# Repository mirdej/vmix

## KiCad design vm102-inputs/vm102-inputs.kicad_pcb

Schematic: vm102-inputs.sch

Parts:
C101: C; C_0603_1608Metric_Pad1.05x0.95mm_HandSolder
D101, D102: SK6812MINI; LED_SK6812MINI_PLCC4_3.5x3.5mm_P1.75mm
J101, J102, J103, J104, J105, J109, J110, J111: Conn; TestPoint_THTPad_D4.0mm_Drill2.0mm
J106: Conn_01x33_Shielded; Molex_502231-3300_1x33-1SH_P0.5mm_Vertical
J107: Conn; TestPoint_THTPad_D3.0mm_Drill1.5mm
SW101, SW102: SW_SPDT; PinSocket_1x03_P2.54mm_Vertical

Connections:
/a: J106.12, J109.1
/aux: J105.1, J106.18
/b: J106.14, J110.1
/bias: J106.22, J107.1
/c: J106.16, J111.1
/compa-out: J102.1, J106.2
/hi_clip1: J106.8, SW102.1 (A)
/hi_clip2: J106.7, SW102.2 (B)
/lo_clip1: J106.4, SW101.1 (A)
/lo_clip2: J106.5, SW101.2 (B)
/output: J103.1, J106.6
/pixels: D101.3 (DIN), J106.10
/scale: J104.1, J106.20
/siff-in: J101.1, J106.24
GND: C101.2, D101.2 (VSS), D102.2 (VSS), J106.1, J106.3, J106.9, J106.13, J106.15, J106.17, J106.19, J106.21, J106.23
unnamed: D101.1 (DOUT), D102.3 (DIN)
VCC: C101.1, D101.4 (VDD), D102.4 (VDD), J106.11

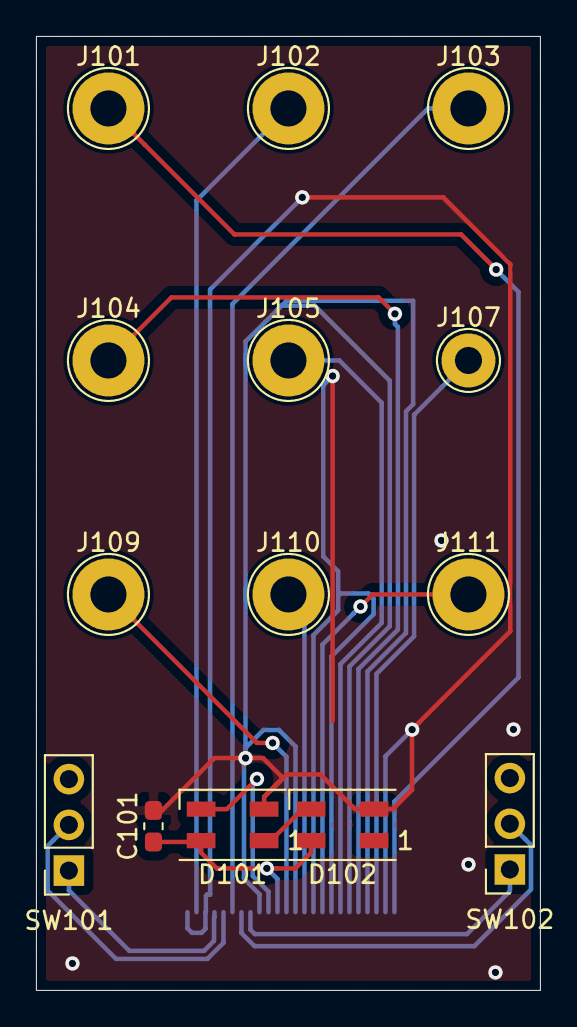
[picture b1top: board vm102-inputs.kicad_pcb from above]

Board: 2 copper layers, 28.0 x 53.0 mm, 15 parts (1 on the bottom side), 17 nets.

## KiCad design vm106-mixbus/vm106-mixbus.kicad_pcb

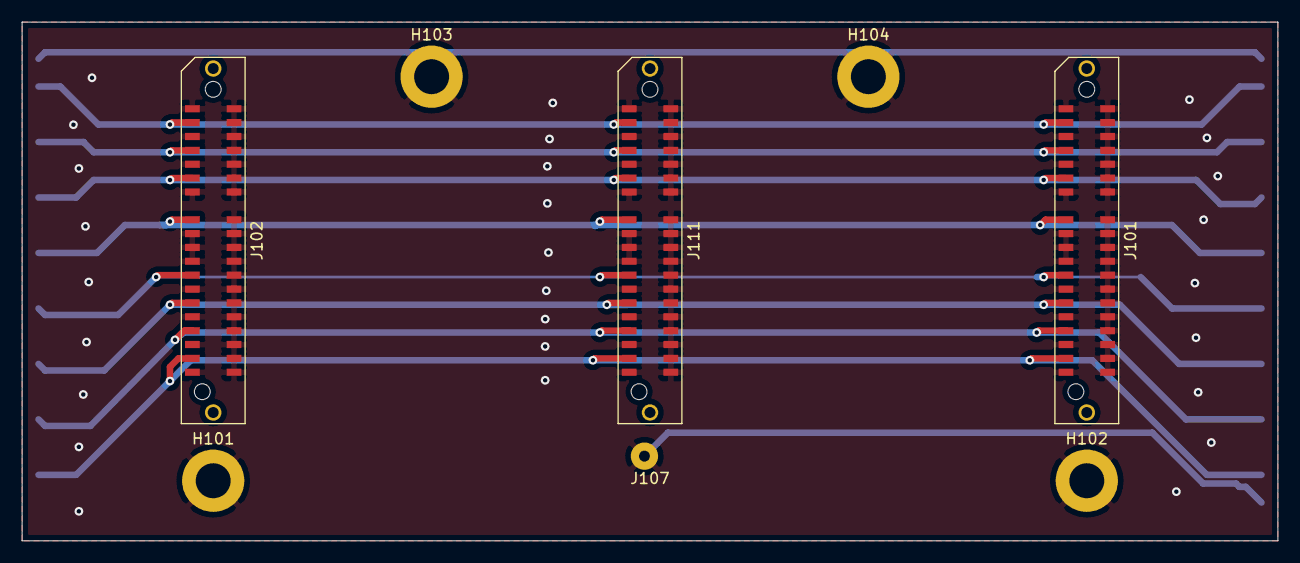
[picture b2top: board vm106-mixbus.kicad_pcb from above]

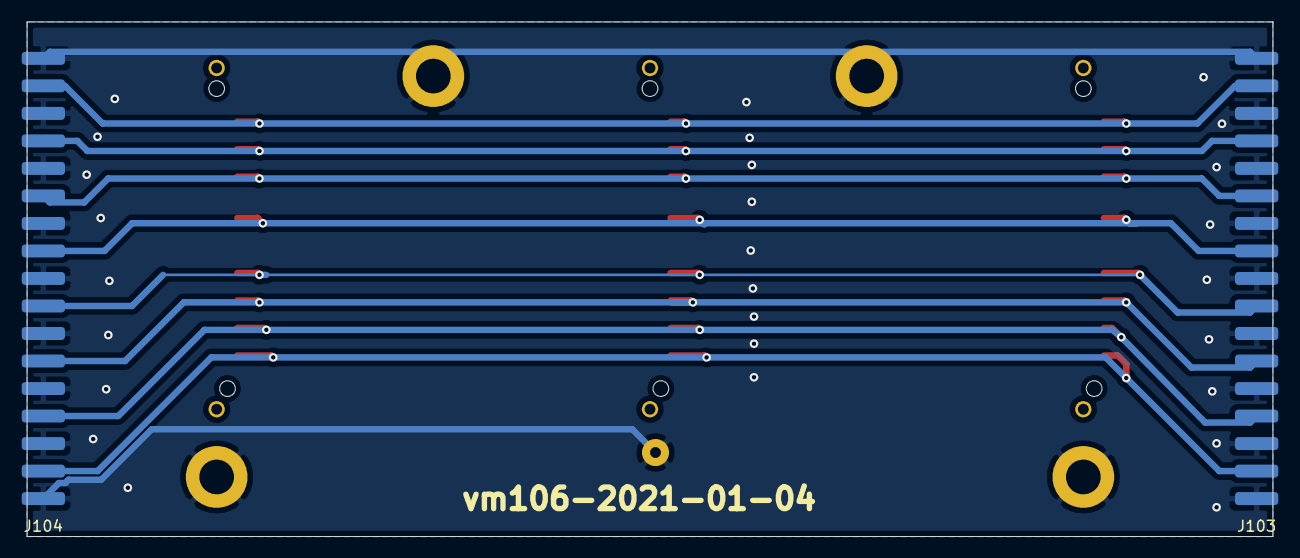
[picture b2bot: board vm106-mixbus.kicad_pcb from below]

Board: 2 copper layers, 115.0 x 47.5 mm, 10 parts (2 on the bottom side), 9 nets.

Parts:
H101, H102, H103, H104: MountingHole_Pad; MountingHole_3.2mm_M3_ISO7380_Pad
J101, J102, J111: Card-Edge_02x20_Odd_Even; Samtec_MECF-20-01-L-DV-WT_2x20_P1.27mm_Polarized_Socket_Hor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
J103, J104: Conn_01x17; 17pin-smd
J107: gnd; Solderpad_1mm

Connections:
GND: H101.1, H102.1, H103.1, H104.1, J101.1, J101.2, J101.4, J101.5, J101.6, J101.8, J101.9, J101.10, J101.12, J101.13, J101.14, J101.18, J101.19, J101.20, J101.21, J101.22, J101.23, J101.24, J101.26, J101.27, J101.28, J101.30, J101.31, J101.32, J101.34, J101.35, J101.36, J101.38, J101.39, J101.40, J102.1, J102.2, J102.4, J102.5, J102.6, J102.8, J102.9, J102.10, J102.12, J102.13, J102.14, J102.18, J102.19, J102.20, J102.21, J102.22, J102.23, J102.24, J102.26, J102.27, J102.28, J102.30, J102.31, J102.32, J102.34, J102.35, J102.36, J102.38, J102.39, J102.40, J103.1, J103.3, J103.5, J103.7, J103.9, J103.11, J103.13, J103.15, J103.17, J104.1, J104.3, J104.5, J104.7, J104.9, J104.11, J104.13, J104.15, J104.17, J107.1, J111.1, J111.2, J111.4, J111.5, J111.6, J111.8, J111.9, J111.10, J111.12, J111.13, J111.14, J111.18, J111.19, J111.20, J111.21, J111.22, J111.23, J111.24, J111.26, J111.27, J111.28, J111.30, J111.31, J111.32, J111.34, J111.35, J111.36, J111.38, J111.39, J111.40
genlock: J101.17, J102.17, J103.8, J104.8, J111.17
hsync: J101.7, J102.7, J103.4, J104.4, J111.7
out_a: J101.25, J102.25, J103.10, J104.10, J111.25
out_b: J101.29, J102.29, J103.12, J104.12, J111.29
out_c: J101.33, J102.33, J103.14, J104.14, J111.33
out_d: J101.37, J102.37, J103.16, J104.16, J111.37
porch: J101.3, J102.3, J103.2, J104.2, J111.3
vsync: J101.11, J102.11, J103.6, J104.6, J111.11

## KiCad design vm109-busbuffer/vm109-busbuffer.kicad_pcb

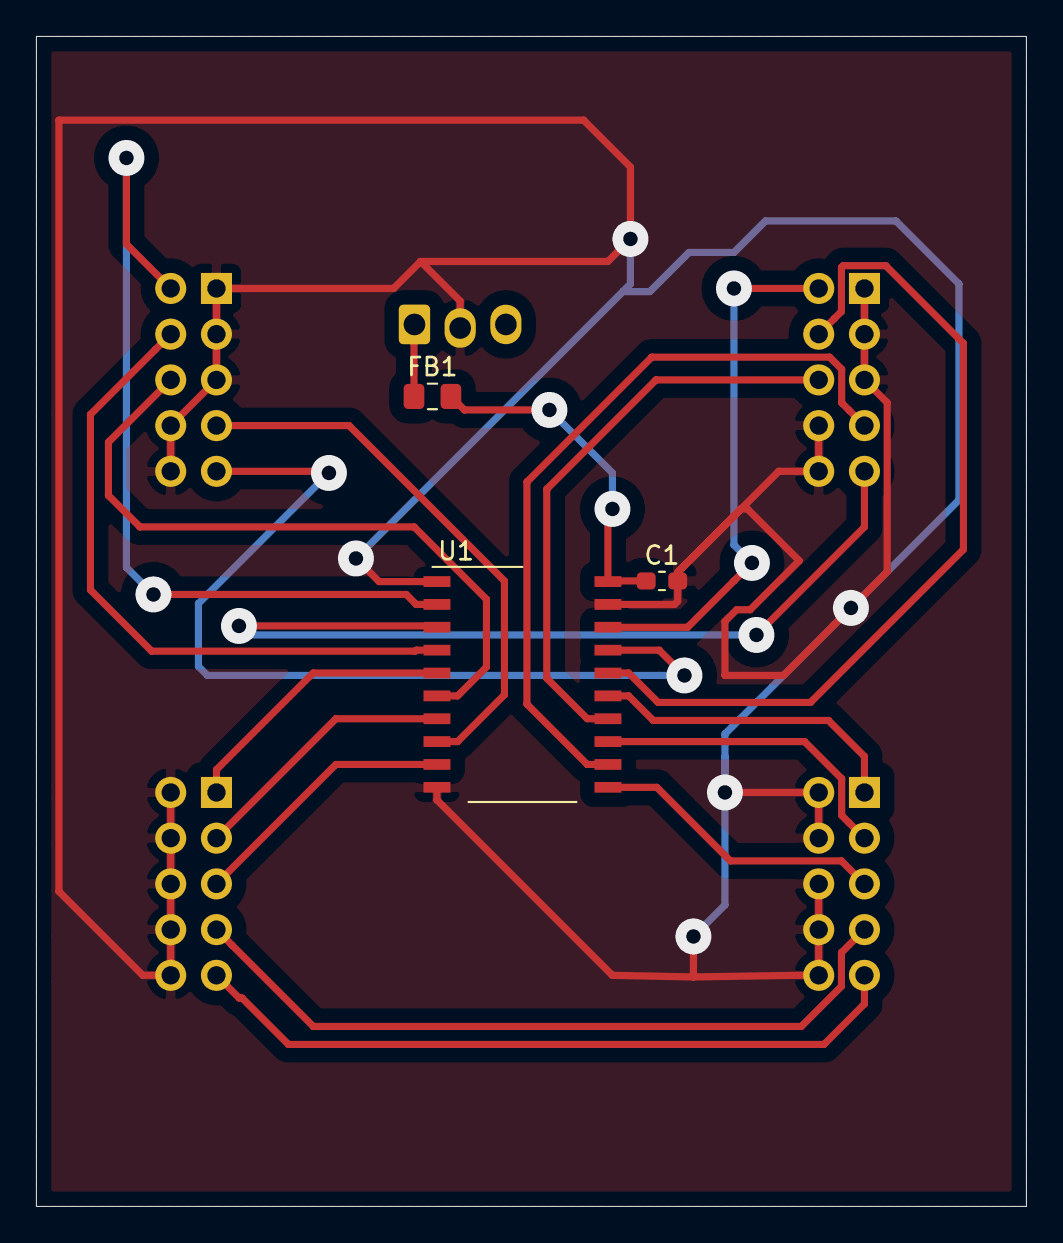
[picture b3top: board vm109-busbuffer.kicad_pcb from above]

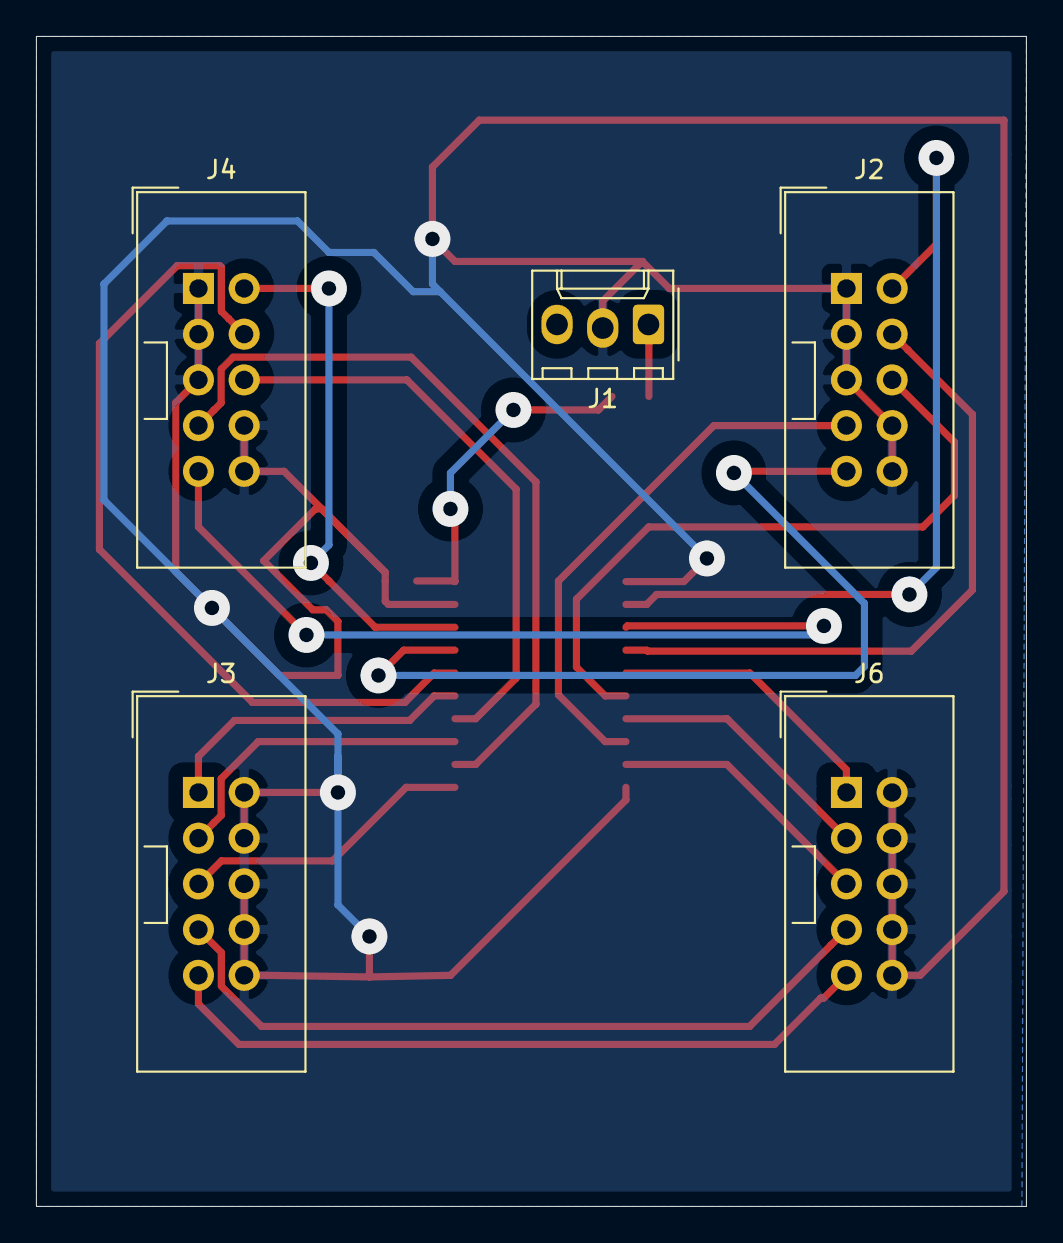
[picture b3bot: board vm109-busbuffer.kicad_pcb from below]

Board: 2 copper layers, 55.0 x 65.0 mm, 8 parts (5 on the bottom side), 21 nets.

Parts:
C1: C; R_0603_1608Metric_Pad1.05x0.95mm_HandSolder
FB1: Ferrite_Bead; L_0805_2012Metric_Pad1.15x1.40mm_HandSolder
J1: Supply; Molex_KK-254_AE-6410-03A_1x03_P2.54mm_Vertical
J2: Syncbus-IN; IDC-Header_2x05_P2.54mm_Vertical
J3: Digitalbus-IN; IDC-Header_2x05_P2.54mm_Vertical
J4: Syncbus; IDC-Header_2x05_P2.54mm_Vertical
J6: Digitalbus; IDC-Header_2x05_P2.54mm_Vertical
U1: 74HC244; SO-20_12.8x7.5mm_P1.27mm

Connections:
+5V: C1.1, FB1.2, U1.20
/scl: J3.9, J6.9
/sda: J3.7, J6.7
/supply+: FB1.1, J1.1
GND: C1.2, J1.2, J2.1, J2.3, J2.5, J2.8, J2.10, J3.2, J3.4, J3.6, J3.8, J3.10, J4.1, J4.3, J4.5, J4.8, J4.10, J6.2, J6.4, J6.6, J6.8, J6.10, U1.1, U1.10, U1.19
unnamed: J2.2, U1.2
unnamed: J2.4, U1.4
unnamed: J2.6, U1.6
unnamed: J2.7, U1.8
unnamed: J2.9, U1.17
unnamed: J3.1, U1.15
unnamed: J3.3, U1.13
unnamed: J3.5, U1.11
unnamed: J4.2, U1.18
unnamed: J4.4, U1.16
unnamed: J4.6, U1.14
unnamed: J4.7, U1.12
unnamed: J4.9, U1.3
unnamed: J6.1, U1.5
unnamed: J6.3, U1.7
unnamed: J6.5, U1.9

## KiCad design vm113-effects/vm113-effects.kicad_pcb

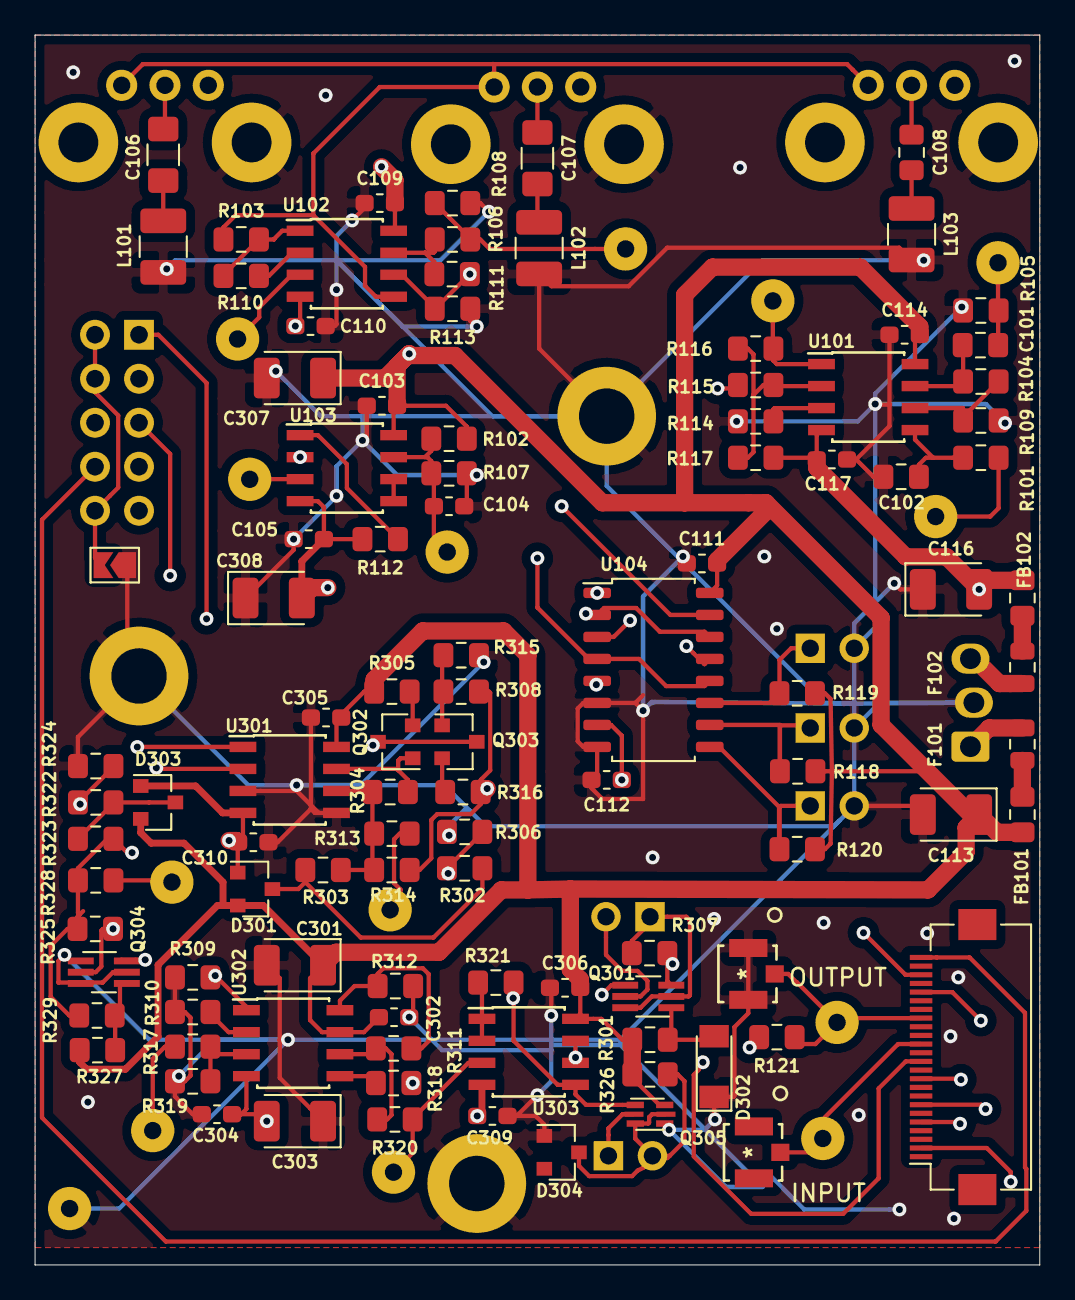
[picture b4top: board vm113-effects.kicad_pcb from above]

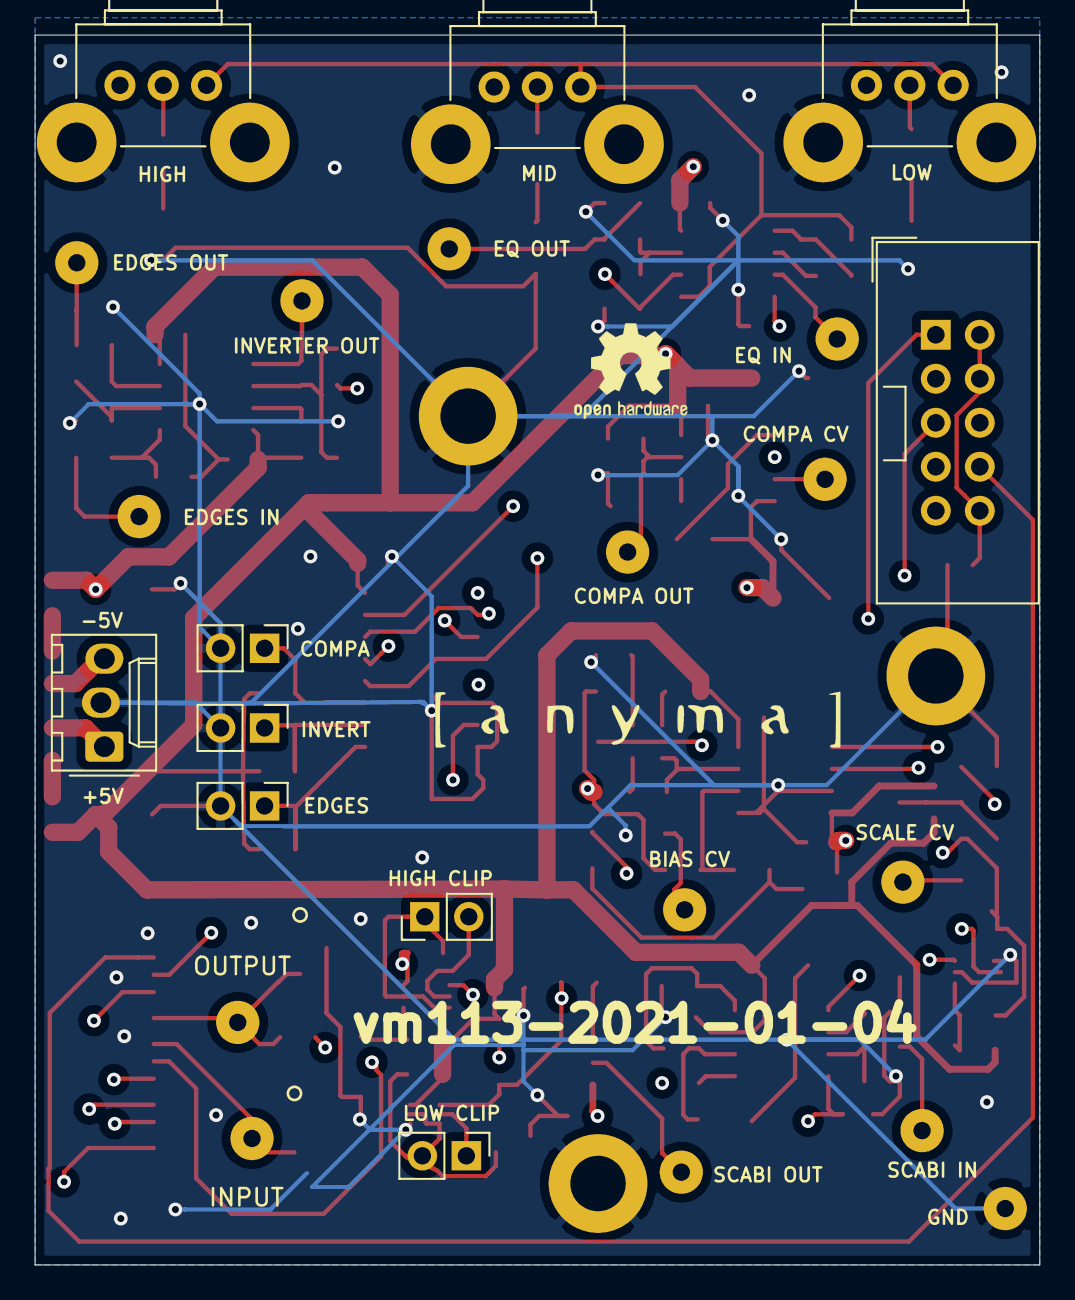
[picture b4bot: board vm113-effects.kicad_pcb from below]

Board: 4 copper layers, 58.0 x 71.0 mm, 132 parts (12 on the bottom side), 70 nets.

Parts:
C101: 1n; C_0805_2012Metric_Pad1.15x1.40mm_HandSolder
C102: 100p; C_0805_2012Metric_Pad1.15x1.40mm_HandSolder
C103, C105, C109, C110, C111, C112, C114, C117, C302, C304, C305, C306, C309, C310: 100n; C_0603_1608Metric_Pad1.05x0.95mm_HandSolder
C104: 100p-470p?; C_0603_1608Metric_Pad1.05x0.95mm_HandSolder
C106: 2u; C_1206_3216Metric_Pad1.42x1.75mm_HandSolder
C107: 300n; C_1206_3216Metric_Pad1.42x1.75mm_HandSolder
C108: 210p; C_0805_2012Metric_Pad1.15x1.40mm_HandSolder
C113, C116, C307, C308: 10u; CP_EIA-3528-21_Kemet-B_Pad1.50x2.35mm_HandSolder
C301, C303: 4u7; CP_EIA-3528-21_Kemet-B_Pad1.50x2.35mm_HandSolder
D301, D303: BAT54S; SOT-23
D302: D; D_MiniMELF
D304: BAT54; D_SOT-23_ANK
F101, F102: Polyfuse; Fuse_0805_2012Metric
FB101, FB102: 330u; L_0805_2012Metric_Pad1.15x1.40mm_HandSolder
H201, H202, H203: MountingHole_Pad; MountingHole_3.2mm_M3_ISO7380_Pad
J101: To 101; Hirose_FH12-24S-0.5SH_1x24-1MP_P0.50mm_Horizontal
J102: INPUT; Solderpad_1mm
J103: EDGES_IN; Solderpad_1mm
J104: OUTPUT; Solderpad_1mm
J105: EQ_IN; Solderpad_1mm
J106: EQ_OUT; Solderpad_1mm
J107: EDGES_OUT; Solderpad_1mm
J108: COMPA-DROP; Solderpad_1mm
J109: INVERTER-DROP; Solderpad_1mm
J110: FROM CTL; IDC-Header_2x05_P2.54mm_Vertical
J111: Power; Molex_KK-254_AE-6410-03A_1x03_P2.54mm_Vertical
J112: gnd; Solderpad_1mm
J113, J114, J115: Jumper; PinHeader_1x02_P2.54mm_Vertical
J116, J117, J118: TP; Solderpad_1mm
J119, J120: UMCC; TE_UMCC_2337019-1
J301, J304: Conn_01x02; PinHeader_1x02_P2.54mm_Vertical
J302: SCABI_OUT; Solderpad_1mm
J303: SCABI_IN; Solderpad_1mm
JP102: Jumper; SolderJumper-2_P1.3mm_Open_TrianglePad1.0x1.5mm
L101: 330u; L_1210_3225Metric_Pad1.42x2.65mm_HandSolder
L102: 330uH; L_1210_3225Metric_Pad1.42x2.65mm_HandSolder
L103: 1.19uH; L_1210_3225Metric_Pad1.42x2.65mm_HandSolder
Q301, Q304: PMBT3906YS; SOT-363_SC-70-6_Handsoldering
Q302: PNP; SOT-23_BEC
Q303: BC847; SOT-23_BEC
Q305: PEMX1; SOT-666
R101, R311, R318, R319: 1k; R_0805_2012Metric_Pad1.15x1.40mm_HandSolder
R102, R309, R321: 300; R_0805_2012Metric_Pad1.15x1.40mm_HandSolder
R103, R111, R113, R114, R115, R116: 2k2; R_0805_2012Metric_Pad1.15x1.40mm_HandSolder
R104: 30k; R_0805_2012Metric_Pad1.15x1.40mm_HandSolder
R105, R312: 100; R_0805_2012Metric_Pad1.15x1.40mm_HandSolder
R106, R107, R108, R110, R121, R302, R320, R322: 75; R_0805_2012Metric_Pad1.15x1.40mm_HandSolder
R109, R118, R119, R120, R314: 15k; R_0805_2012Metric_Pad1.15x1.40mm_HandSolder
R112: 220; R_0805_2012Metric_Pad1.15x1.40mm_HandSolder
R117: 16k; R_0805_2012Metric_Pad1.15x1.40mm_HandSolder
R301: 120; R_0805_2012Metric_Pad1.15x1.40mm_HandSolder
R303, R304, R306, R308, R315, R317, R324, R327: 10k; R_0805_2012Metric_Pad1.15x1.40mm_HandSolder
R305, R316: 3k3; R_0805_2012Metric_Pad1.15x1.40mm_HandSolder
R307: 5k6; R_0805_2012Metric_Pad1.15x1.40mm_HandSolder
R310: 560; R_0805_2012Metric_Pad1.15x1.40mm_HandSolder
R313: 5.1k; R_0805_2012Metric_Pad1.15x1.40mm_HandSolder
R323, R328: 100k; R_0805_2012Metric_Pad1.15x1.40mm_HandSolder
R325, R329: 4k7; R_0805_2012Metric_Pad1.15x1.40mm_HandSolder
R326: 47k; R_0805_2012Metric_Pad1.15x1.40mm_HandSolder
RV101: LOW; Potentiometer_Alps_RK09K_Single_Horizontal
RV102: MID; Potentiometer_Alps_RK09K_Single_Horizontal
RV103: HIGH; Potentiometer_Alps_RK09K_Single_Horizontal
U101, U102, U301, U303: LMH6643; SOIC-8_3.9x4.9mm_P1.27mm
U103: LM311; SOIC-8_3.9x4.9mm_P1.27mm
U104: MAX4053; SOP-16_4.55x10.3mm_P1.27mm
U201: LOGO; logo_anyma
U202: LOGO; OSHW-Logo2_7.3x6mm_SilkScreen
U302: LT1228; SOIC-8_3.9x4.9mm_P1.27mm

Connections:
+5V: C103.2, C109.2, C111.2, C113.1, C114.2, C301.1, C302.2, C305.2, C306.2, C307.1, D301.2, D303.2, FB101.2, Q305.6, R102.1, R118.1, R119.1, R120.1, R301.1, R305.1, R326.1, R327.1, U101.8, U102.8, U103.8, U104.16, U301.8, U302.7, U303.8
-5V: C105.1, C110.1, C112.1, C116.2, C117.1, C303.2, C304.2, C308.2, C309.1, C310.2, D301.1, D303.1, FB102.2, Q301.3, R112.2, R117.2, R307.2, R314.2, R315.2, R316.2, U101.4, U102.4, U103.4, U104.7, U301.4, U302.4, U303.4
/Scabi/Clip/OUTPUT: R121.2, U303.6, U303.7
/Scabi/Clip/scabi-out: J302.1, R320.1, U303.3
/compa_in: U103.2, U104.4, U104.12
/compa_out: C104.2, J101.2, J108.1, R102.2, R107.1, U103.7, U104.13
/edges_in: J101.14, J102.1, J103.1, J119.1, R101.2, U104.5
/edges_out: C101.2, J107.1, R105.2, U104.3
/eq_in: J105.1, U102.3, U104.15
/eq_out: J106.1, J303.1, R106.1, R108.2, R317.1
/inverter_in: R115.2, U104.2, U104.14
/inverter_out: J109.1, R116.1, U101.1, U104.1
/to-101: J101.17, J104.1, J120.1, R121.1
BIAS-IN: J101.22, R302.1, R306.2
GND: C102.1, C103.1, C104.1, C105.2, C109.1, C110.2, C111.1, C112.2, C113.2, C114.1, C116.1, C117.2, C301.2, C302.1, C303.1, C304.1, C305.1, C306.1, C307.2, C308.1, C309.2, C310.1, D302.1, D304.2, H201.1, H202.1, H203.1, J111.2, J112.1, J113.2, J114.2, J115.2, J120.2, J120.3, JP102.1, L101.2, L102.2, L103.2, Q304.1, Q304.3, Q304.5, Q305.4, R105.1, R107.2, R108.1, R109.2, R113.1, R114.1, R306.1, R308.1, R309.1, R310.1, R312.1, R319.1, R324.1, U104.6, U104.8, U301.3, U301.5
unnamed: C101.1, R104.1, U101.7
unnamed: C102.2, R101.1, U101.5
unnamed: C106.1, RV101.2
unnamed: C106.2, L101.1
unnamed: C107.1, RV102.2
unnamed: C107.2, L102.1
unnamed: C108.1, RV103.2
unnamed: C108.2, L103.1
unnamed: D301.3, R302.2, R303.1
unnamed: D302.2, Q301.1, R301.2
unnamed: D303.3, R322.2, R323.1
unnamed: F101.1, FB101.1
unnamed: F101.2, J111.1
unnamed: F102.1, FB102.1
unnamed: F102.2, J111.3
unnamed: J110.2, J110.4, J110.10, JP102.2
unnamed: Q301.4, Q305.1, R321.1, U303.5
unnamed: Q302.B, R304.2, U301.7
unnamed: Q302.C, Q303.C, R309.2, U302.1
unnamed: Q302.E, R305.2
unnamed: Q303.B, R308.2, R315.1
unnamed: Q303.E, R316.1
unnamed: Q304.2, R325.2, U301.1
unnamed: Q304.4, R327.2, R329.2
unnamed: Q304.6, R318.2
unnamed: R103.1, RV101.1, RV102.1, RV103.1, U102.5
unnamed: R103.2, R110.1, U102.1
unnamed: R104.2, R109.1, U101.6
unnamed: R106.2, R111.1, U102.7
unnamed: R110.2, U102.2
unnamed: R111.2, R113.2, RV101.3, RV102.3, RV103.3, U102.6
unnamed: R112.1, U103.1
unnamed: R114.2, U101.3
unnamed: R115.1, R116.2, R117.1, U101.2
unnamed: R303.2, R304.1, R313.2, R314.1, U301.6
unnamed: R310.2, U302.2
unnamed: R311.1, R320.2, U302.6
unnamed: R311.2, R312.2, U302.8
unnamed: R317.2, R319.2, U302.3
unnamed: R318.1, U302.5
unnamed: R321.2, U303.1, U303.2
unnamed: R323.2, R325.1, R328.2, R329.1, U301.2
unnamed: U103.5, U103.6
SCALE-IN: J101.20, R322.1, R324.2
bias_cv: J110.9, J117.1, R313.1
compa_bypass: J110.6, J114.1, R119.2, U104.11
compa_cv: J110.3, J118.1, U103.3
dry~wet~: J101.24, J110.8
edges_bypass: J110.5, J115.1, R120.2, U104.9
hi_clip_1: J101.12, J301.1, Q301.2, Q301.6, R307.1
hi_clip_2: J101.10, J301.2, Q301.5
inverter_bypass: J110.7, J113.1, R118.2, U104.10
lo_clip_1: J101.5, J304.1, Q305.2
lo_clip_2: D304.1, J101.7, J304.2, Q305.3, Q305.5, R326.2
scale_cv: J110.1, J116.1, R328.1

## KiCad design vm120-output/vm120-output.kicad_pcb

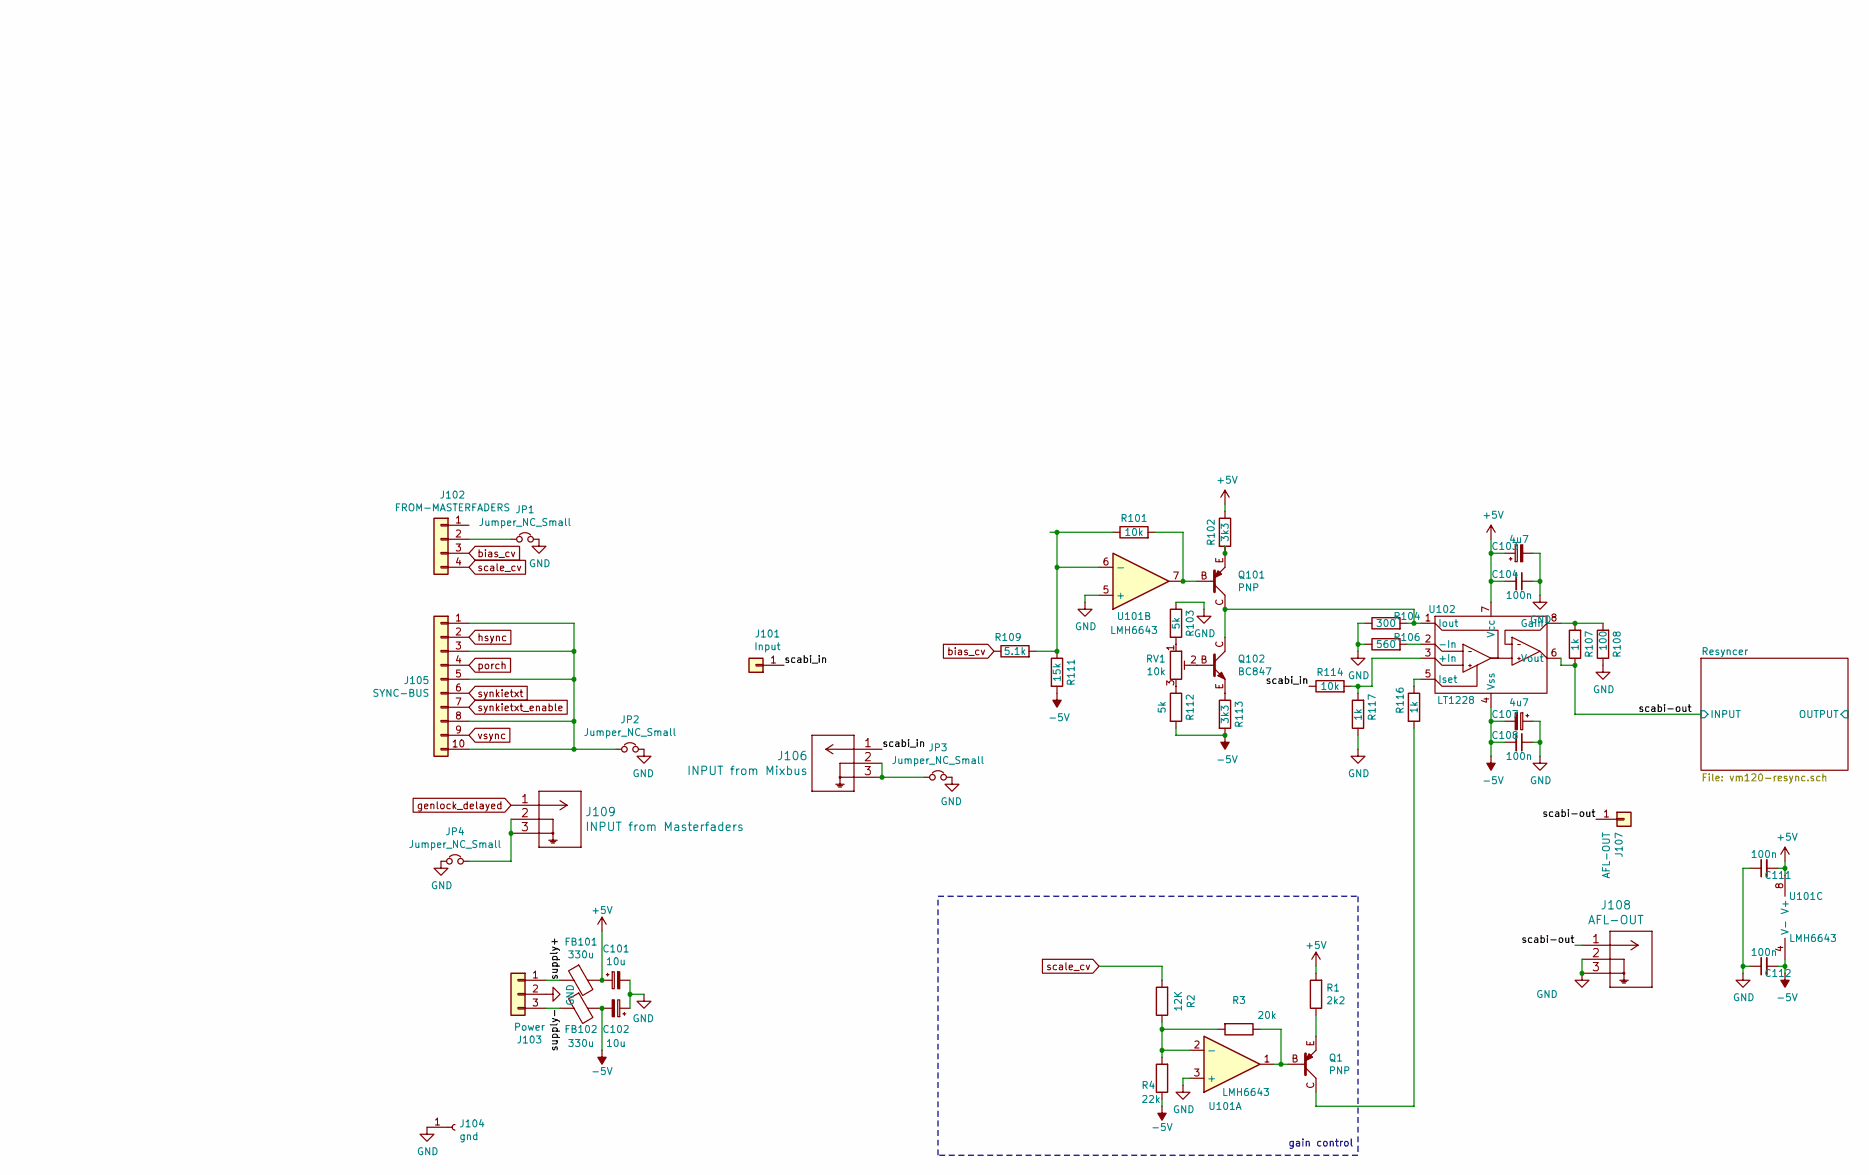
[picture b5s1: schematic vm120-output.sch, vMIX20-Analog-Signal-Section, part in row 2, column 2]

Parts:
C101, C102: 10u; CP_EIA-3528-21_Kemet-B_Pad1.50x2.35mm_HandSolder
C103, C107: 4u7; CP_EIA-3528-21_Kemet-B_Pad1.50x2.35mm_HandSolder
C104, C108, C111, C112: 100n; C_0603_1608Metric_Pad1.05x0.95mm_HandSolder
FB101, FB102: 330u; L_0805_2012Metric_Pad1.15x1.40mm_HandSolder
J101: Input; Solderpad_1mm
J102: FROM-MASTERFADERS; Molex_KK-254_AE-6410-04A_1x04_P2.54mm_Vertical
J103: Power; Molex_KK-254_AE-6410-03A_1x03_P2.54mm_Vertical
J104: gnd; Solderpad_1mm
J105: SYNC-BUS; IDC-Header_2x05_P2.54mm_Vertical
J106: INPUT from Mixbus; TE_UMCC_2337019-1
J107: AFL-OUT; Solderpad_1mm
J108: AFL-OUT; TE_UMCC_2337019-1
J109: INPUT from Masterfaders; TE_UMCC_2337019-1
JP1, JP2, JP3, JP4: Jumper_NC_Small; SolderJumper-2_P1.3mm_Bridged_Pad1.0x1.5mm
Q1, Q101: PNP; SOT-23_BEC
Q102: BC847; SOT-23_BEC
R1: 2k2; R_0805_2012Metric_Pad1.15x1.40mm_HandSolder
R2: 12K; R_0805_2012Metric_Pad1.15x1.40mm_HandSolder
R3: 20k; R_0805_2012Metric_Pad1.15x1.40mm_HandSolder
R4: 22k; R_0805_2012Metric_Pad1.15x1.40mm_HandSolder
R101, R114: 10k; R_0805_2012Metric_Pad1.15x1.40mm_HandSolder
R102, R113: 3k3; R_0805_2012Metric_Pad1.15x1.40mm_HandSolder
R103, R112: 5k; R_0805_2012Metric_Pad1.15x1.40mm_HandSolder
R104: 300; R_0805_2012Metric_Pad1.15x1.40mm_HandSolder
R106: 560; R_0805_2012Metric_Pad1.15x1.40mm_HandSolder
R107, R116, R117: 1k; R_0805_2012Metric_Pad1.15x1.40mm_HandSolder
R108: 100; R_0805_2012Metric_Pad1.15x1.40mm_HandSolder
R109: 5.1k; R_0805_2012Metric_Pad1.15x1.40mm_HandSolder
R111: 15k; R_0805_2012Metric_Pad1.15x1.40mm_HandSolder
RV1: 10k; Potentiometer_Bourns_3296Y_Vertical
U101: LMH6643; SOIC-8_3.9x4.9mm_P1.27mm
U102: LT1228; SOIC-8_3.9x4.9mm_P1.27mm

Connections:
+5V: C101.1, C103.1, C104.2, C111.2, FB101.2, R1.2, R102.1, U101.8 (V+), U102.7 (Vcc); also elsewhere on the board
-5V: C102.2, C107.2, C108.2, C112.2, FB102.2, R4.1, R111.2, R112.2, R113.2, U101.4 (V-), U102.4 (Vss); also elsewhere on the board
/scabi-out: J107.1, J108.1, R107.1, U102.6 (Vout); also elsewhere on the board
/scabi_in: J101.1, J106.1, R114.1
/supply+: FB101.1, J103.1
/supply-: FB102.1, J103.3
GND: C101.2, C102.1, C103.2, C104.1, C107.1, C108.1, C111.1, C112.1, J103.2, J104.1, J108.2, J108.3, JP1.2, JP2.1, JP3.1, JP4.1, R103.1, R104.1, R106.1, R108.1, R117.1, U101.3 (+), U101.5 (+); also elsewhere on the board
unnamed: J102.2, JP1.1
unnamed: J105.1, J105.3, J105.5, J105.8, J105.10, JP2.2
unnamed: J106.2, J106.3, JP3.2
unnamed: J109.2, J109.3, JP4.2
unnamed: Q1.B, R3.1, U101.1
unnamed: Q1.C, R116.2
unnamed: Q1.E, R1.1
unnamed: Q101.B, R101.2, U101.7
unnamed: Q101.C, Q102.C, R104.2, U102.1 (Iout)
unnamed: Q101.E, R102.2
unnamed: Q102.B, RV1.2
unnamed: Q102.E, R113.1
unnamed: R2.1, R3.2, R4.2, U101.2 (-)
unnamed: R101.1, R109.2, R111.1, U101.6 (-)
unnamed: R103.2, RV1.1
unnamed: R106.2, U102.2 (-In)
unnamed: R107.2, R108.2, U102.8 (Gain)
unnamed: R112.1, RV1.3
unnamed: R114.2, R117.2, U102.3 (+In)
unnamed: R116.1, U102.5 (Iset)
bias_cv: J102.3, R109.1
genlock_delayed: J109.1; also elsewhere on the board
hsync: J105.2; also elsewhere on the board
porch: J105.4; also elsewhere on the board
scale_cv: J102.4, R2.2
synkietxt: J105.6; also elsewhere on the board
synkietxt_enable: J105.7; also elsewhere on the board

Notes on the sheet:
gain control

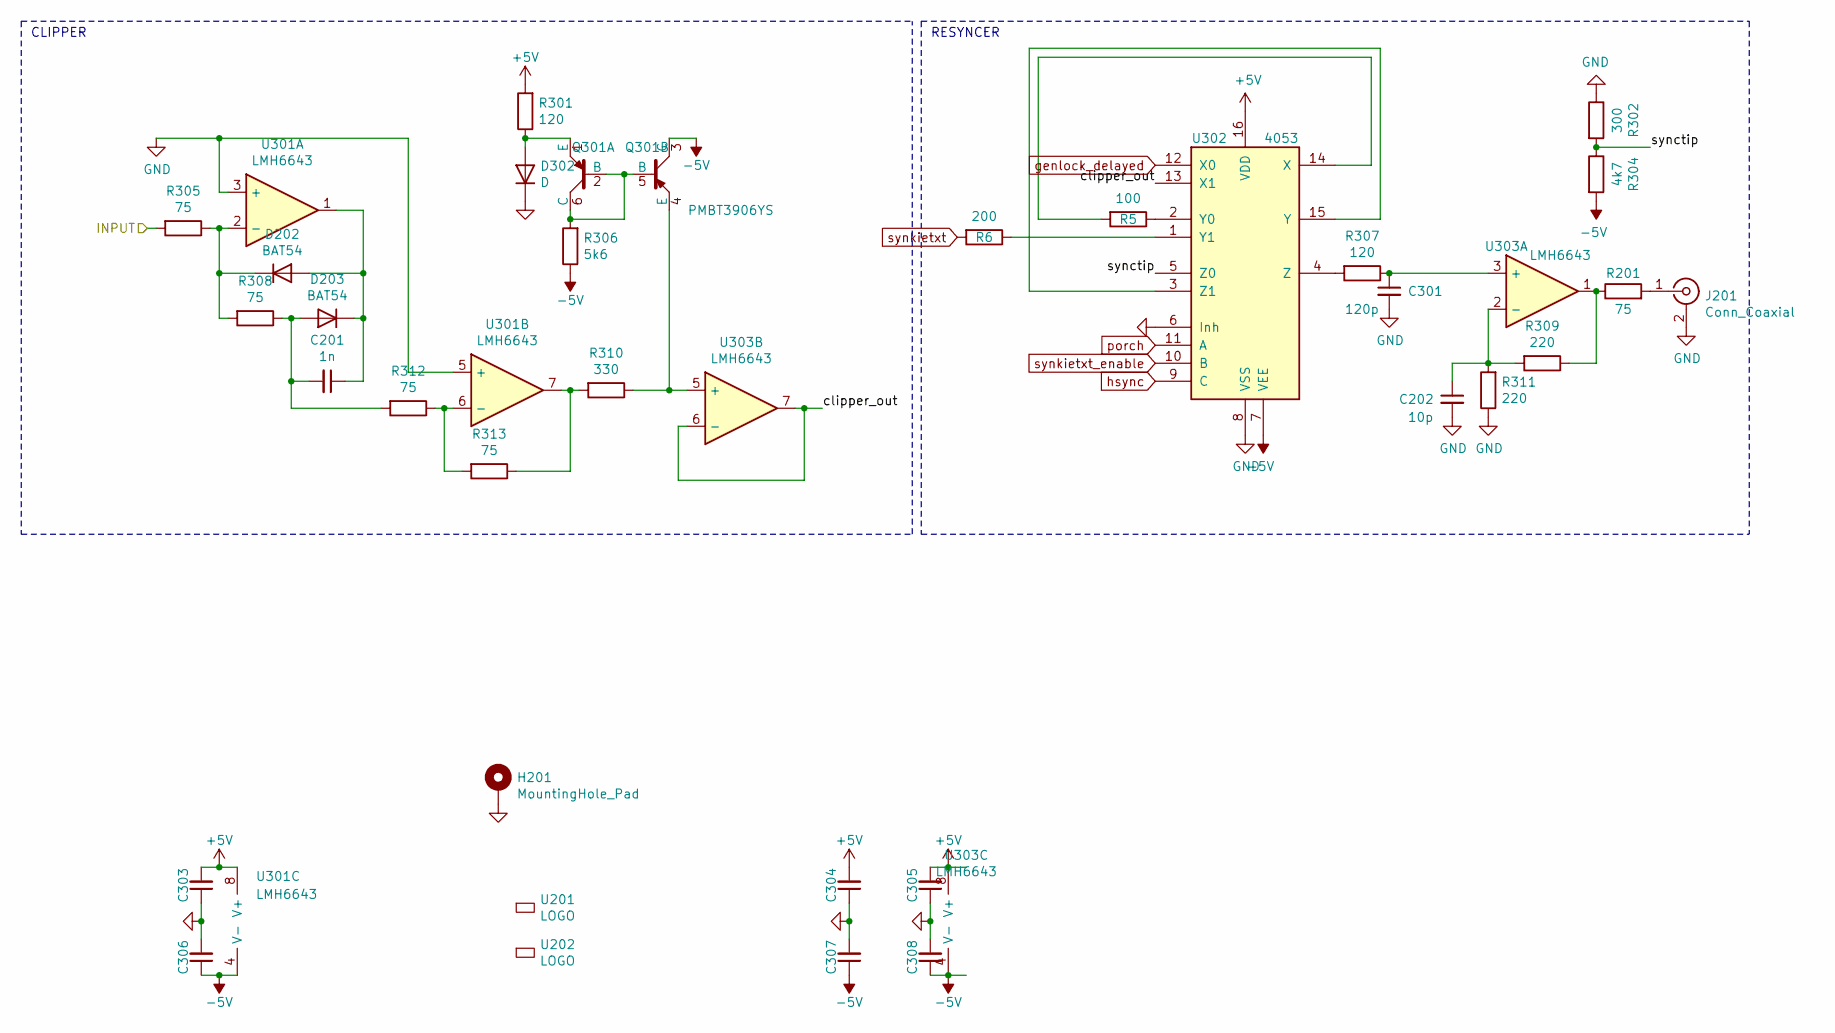
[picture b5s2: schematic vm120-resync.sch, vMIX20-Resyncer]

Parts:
C201: 1n; C_0805_2012Metric_Pad1.15x1.40mm_HandSolder
C202: 10p; C_0603_1608Metric_Pad1.05x0.95mm_HandSolder
C301: 120p; C_0603_1608Metric_Pad1.05x0.95mm_HandSolder
C303, C304, C305, C306, C307, C308: 100n; C_0603_1608Metric_Pad1.05x0.95mm_HandSolder
D202, D203: BAT54; D_SOT-23_ANK
D302: D; D_MiniMELF
H201: MountingHole_Pad; MountingHole_2.7mm_M2.5_DIN965_Pad
J201: Conn_Coaxial; BNC_MOLEX_0731000080_Horizontal
Q301: PMBT3906YS; SOT-363_SC-70-6_Handsoldering
R5: 100; R_0805_2012Metric_Pad1.15x1.40mm_HandSolder
R6: 200; R_0805_2012Metric_Pad1.15x1.40mm_HandSolder
R201, R305, R308, R312, R313: 75; R_0805_2012Metric_Pad1.15x1.40mm_HandSolder
R301, R307: 120; R_0805_2012Metric_Pad1.15x1.40mm_HandSolder
R302: 300; R_0805_2012Metric_Pad1.15x1.40mm_HandSolder
R304: 4k7; R_0805_2012Metric_Pad1.15x1.40mm_HandSolder
R306: 5k6; R_0805_2012Metric_Pad1.15x1.40mm_HandSolder
R309, R311: 220; R_0805_2012Metric_Pad1.15x1.40mm_HandSolder
R310: 330; R_0805_2012Metric_Pad1.15x1.40mm_HandSolder
U201: LOGO; logo_anyma
U202: LOGO; OSHW-Logo2_9.8x8mm_SilkScreen
U301, U303: LMH6643; SOIC-8_3.9x4.9mm_P1.27mm
U302: 4053; SOIC-16_3.9x9.9mm_P1.27mm

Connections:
+5V: C303.2, C304.2, C305.2, R301.2, U301.8 (V+), U302.16 (VDD), U303.8 (V+); also elsewhere on the board
-5V: C306.1, C307.1, C308.1, Q301.3 (C), R304.2, R306.1, U301.4 (V-), U302.7 (VEE), U303.4 (V-); also elsewhere on the board
/Resyncer/clipper_out: U302.13 (X1), U303.6 (-), U303.7
/Resyncer/synctip: R302.2, R304.1, U302.5 (Z0)
/scabi-out: R305.2; also elsewhere on the board
GND: C202.2, C301.2, C303.1, C304.1, C305.1, C306.2, C307.2, C308.2, D302.1 (K), H201.1, J201.2 (Ext), R302.1, R311.1, U301.3 (+), U301.5 (+), U302.6 (Inh), U302.8 (VSS); also elsewhere on the board
unnamed: C201.1, D202.2 (A), D203.1 (K), U301.1
unnamed: C201.2, D203.2 (A), R308.1, R312.2
unnamed: C202.1, R309.2, R311.2, U303.2 (-)
unnamed: C301.1, R307.1, U303.3 (+)
unnamed: D202.1 (K), R305.1, R308.2, U301.2 (-)
unnamed: D302.2 (A), Q301.1 (E), R301.1
unnamed: J201.1 (In), R201.2
unnamed: Q301.2 (B), Q301.5 (B), Q301.6 (C), R306.2
unnamed: Q301.4 (E), R310.1, U303.5 (+)
unnamed: R5.1, U302.2 (Y0)
unnamed: R5.2, U302.14 (X)
unnamed: R6.1, U302.1 (Y1)
unnamed: R201.1, R309.1, U303.1
unnamed: R307.2, U302.4 (Z)
unnamed: R310.2, R313.1, U301.7
unnamed: R312.1, R313.2, U301.6 (-)
unnamed: U302.3 (Z1), U302.15 (Y)
genlock_delayed: U302.12 (X0); also elsewhere on the board
hsync: U302.9 (C); also elsewhere on the board
porch: U302.11 (A); also elsewhere on the board
synkietxt: R6.2; also elsewhere on the board
synkietxt_enable: U302.10 (B); also elsewhere on the board

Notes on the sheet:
CLIPPER
RESYNCER

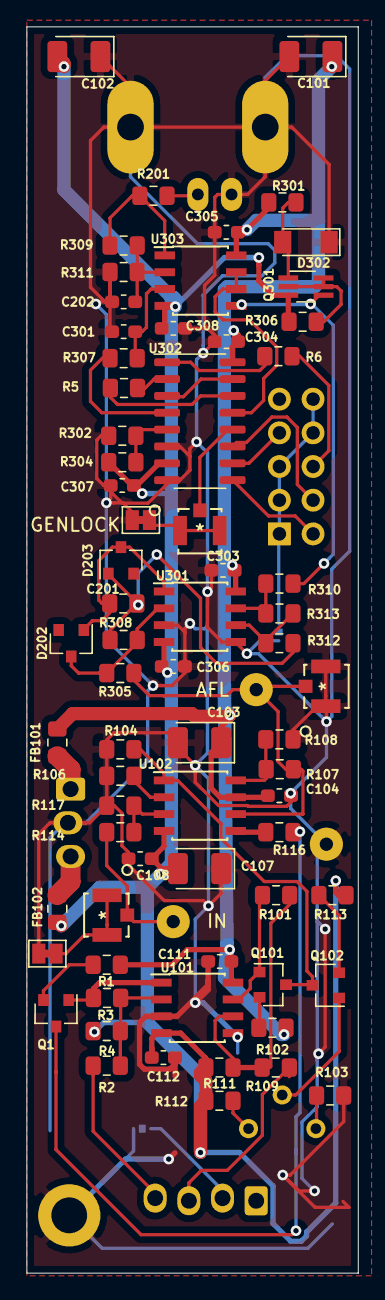
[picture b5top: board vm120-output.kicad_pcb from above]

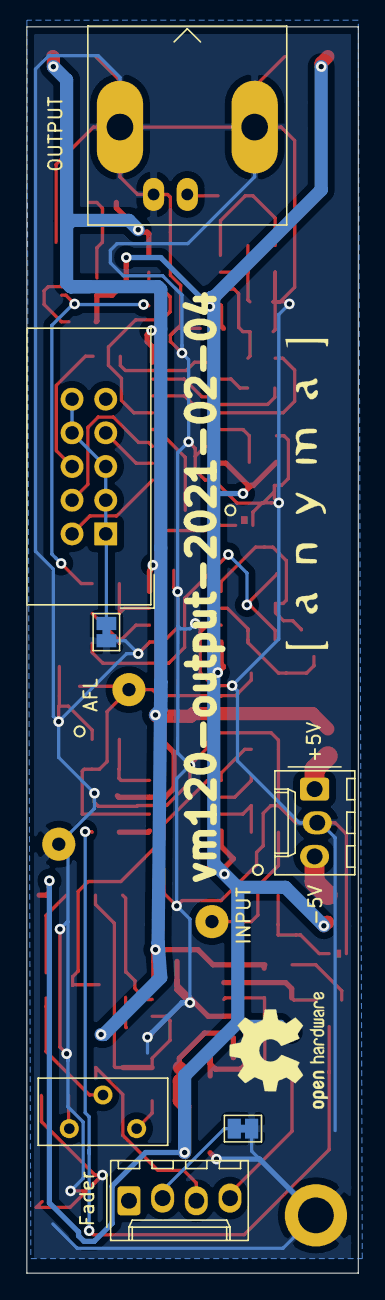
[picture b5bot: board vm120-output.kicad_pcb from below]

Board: 2 copper layers, 25.0 x 94.0 mm, 82 parts (9 on the bottom side), 53 nets.

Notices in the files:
parts and their libraries:
Copyright 2016 Accelerated Designs. All rights reserved.
